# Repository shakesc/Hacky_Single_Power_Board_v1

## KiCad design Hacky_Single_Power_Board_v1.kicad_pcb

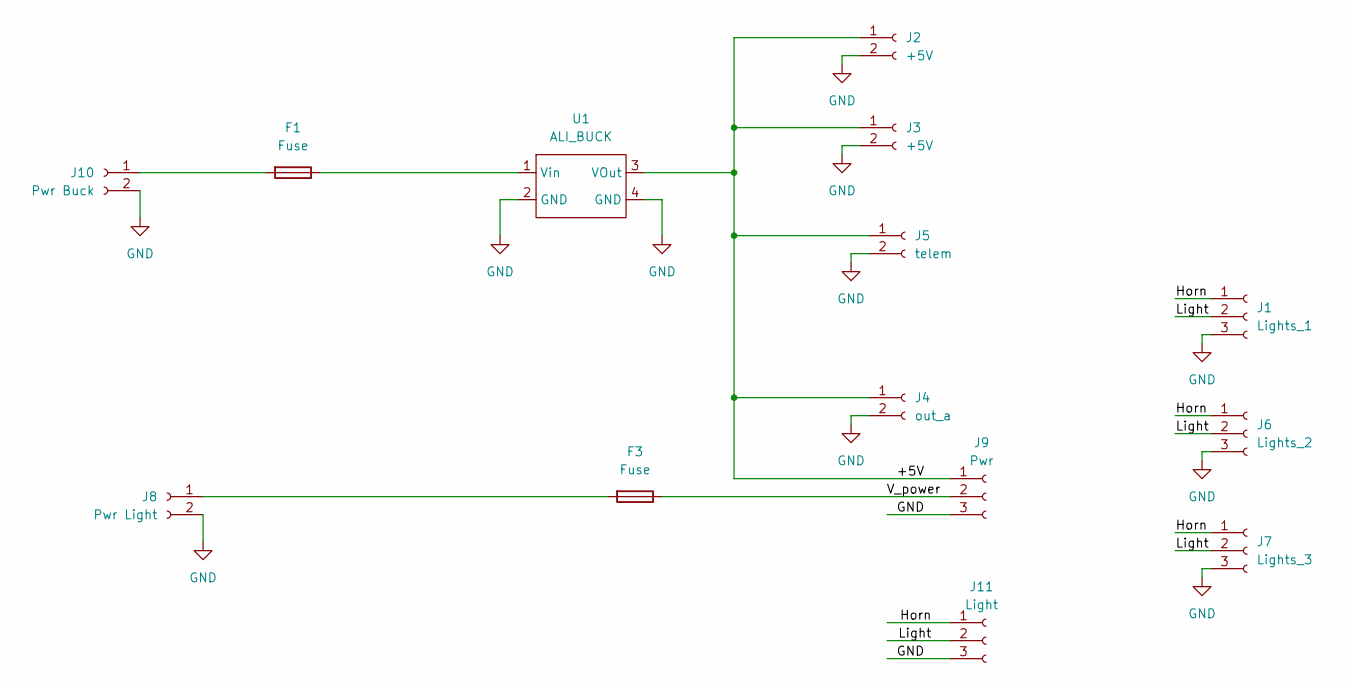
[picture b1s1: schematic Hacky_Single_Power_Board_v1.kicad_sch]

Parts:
F1, F3: Fuse; Fuse_20mm_Holder
J1: Lights_1; JST_XH_B3B-XH-A_1x03_P2.50mm_Vertical
J2, J3: +5V; Molex_KK-396_5273-02A_1x02_P3.96mm_Vertical
J4: out_a; JST_XH_B2B-XH-A_1x02_P2.50mm_Vertical
J5: telem; JST_XH_B2B-XH-A_1x02_P2.50mm_Vertical
J6: Lights_2; JST_XH_B3B-XH-A_1x03_P2.50mm_Vertical
J7: Lights_3; JST_XH_B3B-XH-A_1x03_P2.50mm_Vertical
J8: Pwr Light; Molex_KK-396_5273-02A_1x02_P3.96mm_Vertical
J9: Pwr; JST_VH_B3P-VH_1x03_P3.96mm_Vertical
J10: Pwr Buck; Molex_KK-396_5273-02A_1x02_P3.96mm_Vertical
J11: Light; JST_VH_B3P-VH_1x03_P3.96mm_Vertical
U1: ALI_BUCK; Ali Voltage Regulator

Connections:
/+5V: J2.1, J3.1, J4.1, J5.1, J9.1, U1.3 (VOut)
/Horn: J1.1, J6.1, J7.1, J11.1
/Light: J1.2, J6.2, J7.2, J11.2
/V_power: F3.1, J9.2
GND: J1.3, J2.2, J3.2, J4.2, J5.2, J6.3, J7.3, J8.2, J9.3, J10.2, J11.3, U1.2 (GND), U1.4 (GND)
unnamed: F3.2, J8.1
unnamed: F1.2, J10.1
unnamed: F1.1, U1.1 (Vin)

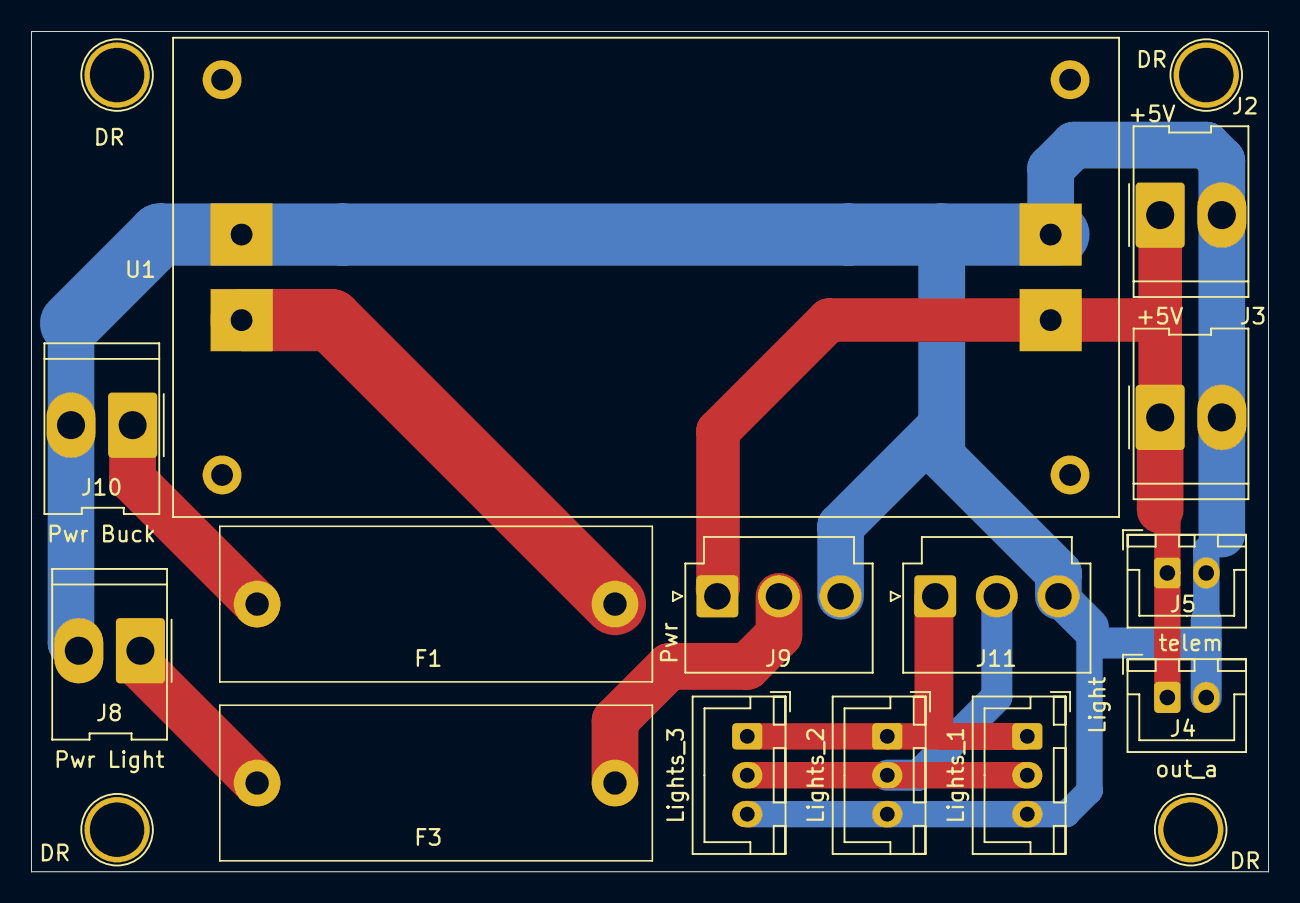
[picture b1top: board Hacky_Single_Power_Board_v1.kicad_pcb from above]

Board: 2 copper layers, 79.5 x 54.0 mm, 18 parts (0 on the bottom side), 8 nets.

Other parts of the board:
DR: drill; Pin_D1.3mm_L11.0mm
DR#2, DR#3, DR#4: drill; Pin_D1.3mm_L11.0mm
